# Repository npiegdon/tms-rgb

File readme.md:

# TMS-RGB #

## An RGB mod for systems using TMS9928A and TMS9929A graphics ##

This small adapter board can unlock the potential of many 8-bit systems from the 1980's including the Colecovision, SG-1000, SC-3000, TI-99/4, and more.

This solution introduces zero latency, works in NTSC or PAL systems, doesn't require any tuning, and can be installed easily.  TMS-RGB was developed in 2020 and solves all known issues found in previous TMS992xA mods of this kind.

Visit [https://tms-rgb.com](https://tms-rgb.com) for more information.

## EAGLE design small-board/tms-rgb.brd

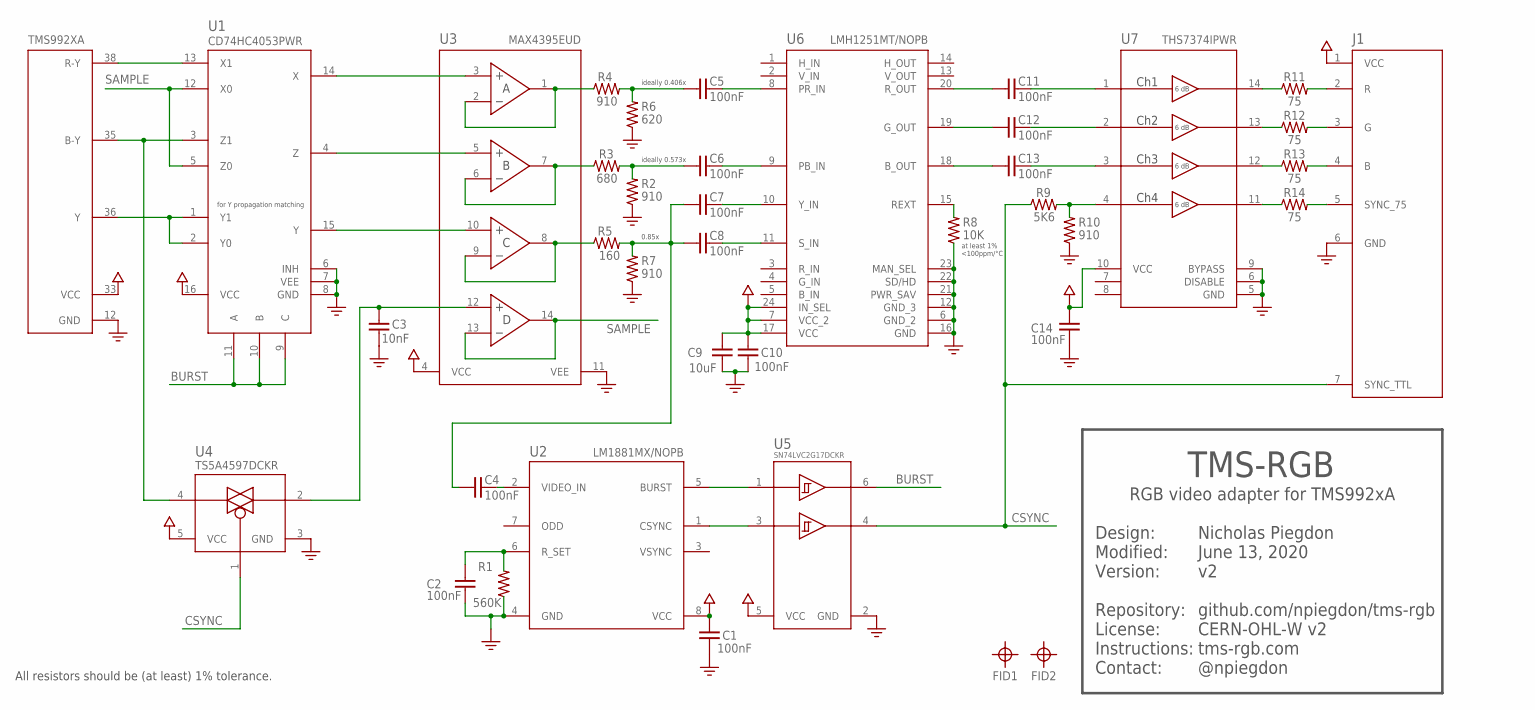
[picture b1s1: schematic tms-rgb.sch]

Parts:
C1, C2, C4, C5, C6, C7, C8, C10, C11, C12, C13, C14: 100nF; C0603
C3: 10nF; C0603
C9: 10uF; C1206
FID1, FID2: FIDUCIAL
J1: Pads; PADS
R1: 560K; R0603
R2, R4, R7, R10: 910; R0603
R3: 680; R0603
R5: 160; R0603
R6: 620; R0603
R8: 10K; R0603
R9: 5K6; R0603
R11, R12, R13, R14: 75; R0603
U1: CD74HC4053PWR; CD74HC4053
U2: LM1881MX/NOPB; LM1881
U3: MAX4395EUD; MAX4395
U4: TS5A4597DCKR; DCK5
U5: SN74LVC2G17DCKR; DCK6
U6: LMH1251MT/NOPB; LMH1251
U7: THS7374IPWR; THS7374
U100: TMS992XA

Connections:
B: J1.4 (B), R13.2
B-Y: U1.3 (Z1), U4.4 (NC), U100.35 (B-Y)
BURST: U1.9 (C), U1.10 (B), U1.11 (A), U5.6 (1Y)
CSYNC: J1.7 (SYNC_TTL), R9.1, U4.1 (IN), U5.4 (2Y)
G: J1.3 (G), R12.2
GND: C1.2, C2.2, C3.2, C9.2, C10.2, C14.2, J1.6 (GND), R1.1, R2.1, R6.1, R7.1, R8.1, R10.1, U1.6 (INH), U1.7 (VEE), U1.8 (GND), U2.4 (GND), U3.11 (VEE), U4.3 (GND), U5.2 (GND), U6.6 (GND_2), U6.12 (GND_3), U6.16 (GND), U6.21 (PWR_SAV), U6.22 (SD/HD), U6.23 (MAN_SEL), U7.5 (GND), U7.6 (DISABLE), U7.9 (BYPASS), U100.12 (GND)
HOLD: C3.1, U3.12 (D+), U4.2 (COM)
MX_B: U1.4 (Z), U3.5 (B+)
MX_R: U1.14 (X), U3.3 (A+)
MX_Y: U1.15 (Y), U3.10 (C+)
unnamed: R4.1, U3.1 (A), U3.2 (A-)
unnamed: R3.1, U3.6 (B-), U3.7 (B)
unnamed: R5.1, U3.8 (C), U3.9 (C-)
unnamed: U2.5 (BURST), U5.1 (1A)
unnamed: U2.1 (CSYNC), U5.3 (2A)
unnamed: C2.1, R1.2, U2.6 (R_SET)
unnamed: R8.2, U6.15 (REXT)
unnamed: R14.1, U7.11 (CH4OUT)
unnamed: R9.2, R10.2, U7.4 (CH4IN)
unnamed: R13.1, U7.12 (CH3OUT)
unnamed: R12.1, U7.13 (CH2OUT)
unnamed: R11.1, U7.14 (CH1OUT)
unnamed: C4.2, U2.2 (VIDEO_IN)
unnamed: C5.2, U6.8 (PR_IN)
unnamed: C6.2, U6.9 (PB_IN)
unnamed: C8.2, U6.11 (S_IN)
unnamed: C7.2, U6.10 (Y_IN)
unnamed: C11.1, U6.20 (R_OUT)
unnamed: C12.1, U6.19 (G_OUT)
unnamed: C13.1, U6.18 (B_OUT)
unnamed: C11.2, U7.1 (CH1IN)
unnamed: C12.2, U7.2 (CH2IN)
unnamed: C13.2, U7.3 (CH3IN)
R: J1.2 (R), R11.2
R-Y: U1.13 (X1), U100.38 (R-Y)
S75: J1.5 (SYNC_75), R14.2
SAMPLE: U1.5 (Z0), U1.12 (X0), U3.13 (D-), U3.14 (D)
SC_B: C6.1, R2.2, R3.2
SC_R: C5.1, R4.2, R6.2
SC_Y: C4.1, C7.1, C8.1, R5.2, R7.2
VCC: C1.1, C9.1, C10.1, C14.1, J1.1 (VCC), U1.16 (VCC), U2.8 (VCC), U3.4 (VCC), U4.5 (VCC), U5.5 (VCC), U6.7 (VCC_2), U6.17 (VCC), U6.24 (IN_SEL), U7.10 (VCC), U100.33 (VCC)
Y: U1.1 (Y1), U1.2 (Y0), U100.36 (Y)

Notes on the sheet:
Nicholas Piegdon June 13, 2020 v2 github.com/npiegdon/tms-rgb CERN-OHL-W v2 tms-rgb.com @npiegdon
Design: Modified: Version: Repository: License: Instructions: Contact:
RGB video adapter for TMS992xA
TMS-RGB
at least 1% <100ppm/°C
All resistors should be (at least) 1% tolerance.
for Y propagation matching
ideally 0.406x
ideally 0.573x
0.85x

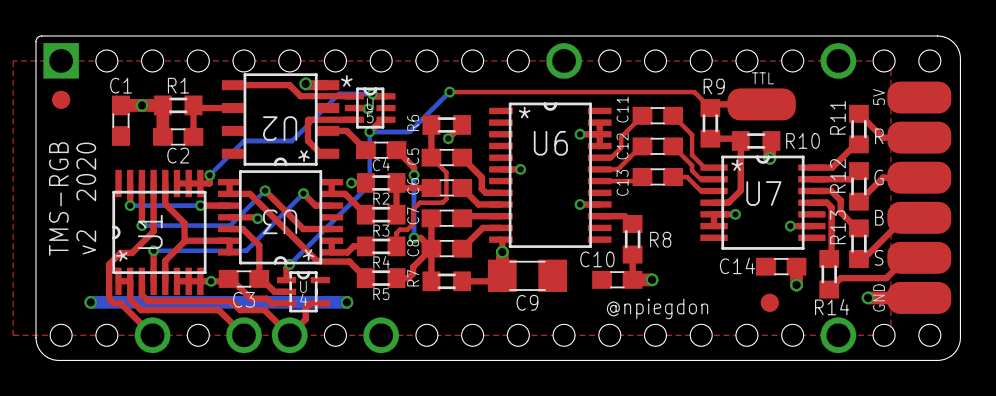
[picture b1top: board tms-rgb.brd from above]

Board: 2 copper layers, 51.4 x 18.0 mm, 39 parts (1 on the bottom side), 42 nets.

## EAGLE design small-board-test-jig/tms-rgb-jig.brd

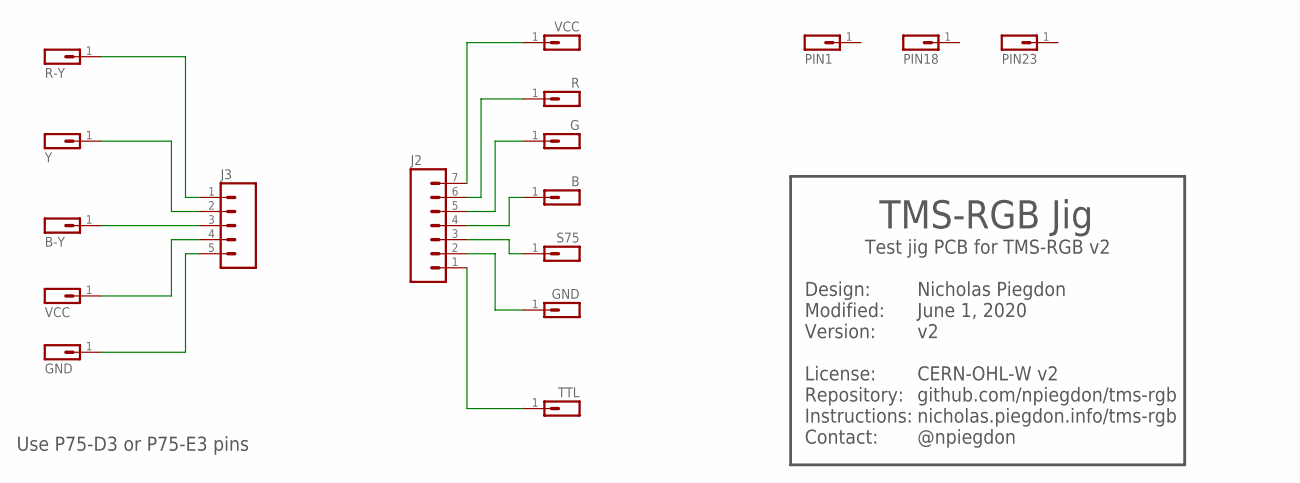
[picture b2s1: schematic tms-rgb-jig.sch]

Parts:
J2: CONN_07; 1X07
J3: CONN_05; 1X05
J4: R-Y; POGO
J5: B-Y; POGO
J6: Y; POGO
J7, J9: VCC; POGO
J8, J14: GND; POGO
J10: R; POGO
J11: G; POGO
J12: B; POGO
J13: S75; POGO
J15: TTL; POGO
J16: PIN1; POGO
J17: PIN18; POGO
J18: PIN23; POGO

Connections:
unnamed: J3.1, J4.1
unnamed: J3.2, J6.1
unnamed: J3.3, J5.1
unnamed: J3.4, J7.1
unnamed: J3.5, J8.1
unnamed: J2.7, J9.1
unnamed: J2.6, J10.1
unnamed: J2.5, J11.1
unnamed: J2.4, J12.1
unnamed: J2.3, J13.1
unnamed: J2.2, J14.1
unnamed: J2.1, J15.1

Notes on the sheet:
Nicholas Piegdon June 1, 2020 v2 CERN-OHL-W v2 github.com/npiegdon/tms-rgb nicholas.piegdon.info/tms-rgb @npiegdon
Design: Modified: Version: License: Repository: Instructions: Contact:
Test jig PCB for TMS-RGB v2
TMS-RGB Jig
Use P75-D3 or P75-E3 pins

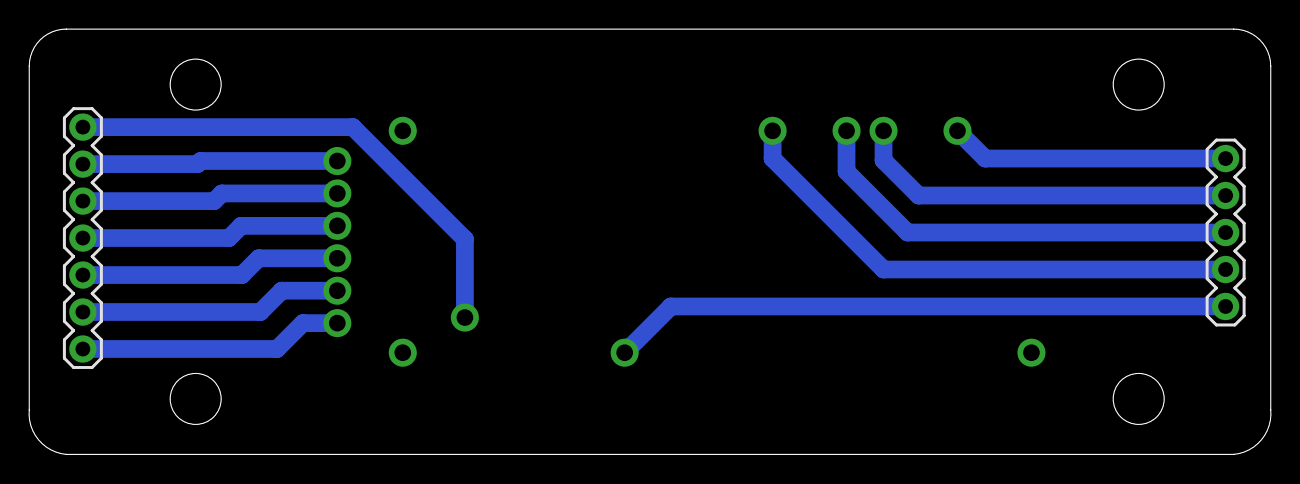
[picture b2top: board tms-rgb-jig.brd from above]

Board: 2 copper layers, 85.3 x 29.2 mm, 17 parts (0 on the bottom side), 12 nets.

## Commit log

2020-05-17 Initial commit; v1 release
2020-05-18 Exclude output pads from stencil
2020-05-21 Nudged C4 on the schematic
    It's the sample-and-hold cap but its position (near the SPST instead of the op-amp) didn't reflect that clearly.
2020-05-22 A few more solderable holes
    That should make mounting it a little stronger. And now pin 1 on the VDP is indicated on both sides with a square through-hole.
2020-05-22 Major layout rework for v2
2020-05-22 Named a few signals
    And bridged a distant VCC fill
2020-05-23 Better label placement
    Still not great, but maybe a little more usable.
2020-06-01 More than 100 improvements
    Nearly all of which were suggested by MrPix from the AtariAge forums to improve the electrical characteristics of the board.
2020-06-01 Update jig for v2
2020-06-02 Updated voltage dividers
    Now we consume around 15mA less with no discernible change to the image.
2020-06-13 Updated instructions URL
    The new place is https://tms-rgb.com
2020-06-13 Readme update
    Added the bare minimum description and updated the instructions URL.
